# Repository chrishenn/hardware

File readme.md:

# Hardware

Projects based on hardware

- arduino thermistor + pwm fan controller
- keyboard pcb
- arduino led touch slider
- arduino light-sensor-driven light-switch
- prusa mk4s machine and filament settings

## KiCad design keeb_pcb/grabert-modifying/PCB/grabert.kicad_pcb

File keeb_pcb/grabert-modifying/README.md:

# Grabert Keyboard Hardware

💻 🖥️ ⌨️ Open-source ~60% Mechanical Keyboard 🎉

Build Guide and additional information [here](doc/BUILDGUIDE.md)!

<details>
  <summary>Screen and Foot</summary>

</details>
<br/>
<details>
  <summary>PCB Images</summary>

</details>
<br/>

[PCB design video](https://youtu.be/ezk02GJ9iMs)

[Case design video](https://youtu.be/DsW-hKeB3mc)

## Features

- OLED Screen
- Rotary Knob
- Sandwich Mount Case
- POM Switch Plate
- [4 Layout Options](doc/BUILDGUIDE.md#preparation-and-layout-decision)
- 32-bit Microcontroller

### Powered by

- [QMK](https://github.com/qmk/qmk_firmware) ([KoBuss QMK Fork](https://github.com/KoBussLLC/qmk_firmware))
- [VIA](https://caniusevia.com/)

## PCB

This project uses KiCad 6 for electrical CAD

### Electrical Design Constraints

- No diode matrix enabled by LQFP 100 MCU Footprint
- 32-bit STM32 Microcontroller (STM32F072V8T6)
- USB-C
- PCB Mount Switches
- PCB Mount Stabilizers
- Push-Button Encoder
- 0.91" 128x32px I2C OLED Display (SSD1306)

### Changes

- V0 had incorrectly valued bypass capacitors. Testing showed no obvious issues, but it is not preferable.

## CAD

This project uses FreeCAD 0.19 for mechanical CAD

### Required Add-ons

- Assembly 4
- Fasteners
- kicadStepUpMod

### Mechanical Design Contraints

- ~60% Keyboard Layout
- 5 Layout Options
- Push Button Encoder
- OLED 128x32 Screen
- Fully Laser Cut Case
- POM Switch Plate
- 2mm diameter fasteners

### Acrylic Sheet Stackup

Main Case Stackup. "0" is the bottom of the case.

| Sheet Number | FreeCAD "Part" | Thickness | Material   | Shape                                    |
| ------------ | -------------- | --------- | ---------- | ---------------------------------------- |
| 0            | bottom         | 0.125 in  | Acrylic    |                    |
| 1            | closed_spacer  | 0.125 in  | Acrylic    |             |
| 2            | usb_spacer     | 0.125 in  | Acrylic    |  \*with feet   |
| 3            | usb_spacer     | 0.125 in  | Acrylic    |  \*with feet   |
| 4            | switch_plate   | 0.0625 in | POM/Acetal |         |
| 5            | closed_spacer  | 0.125 in  | Acrylic    |             |
| 6            | colored_top    | 0.125 in  | Acrylic    |  |
| 7            | clear_top      | 0.125 in  | Acrylic    |                 |

#### Angled Foot Stackup

Foot stackup. "0" is closest to the case and is on the "top"

| Sheet Number | FreeCAD "Part" | Thickness | Material |
| ------------ | -------------- | --------- | -------- |
| 0            | foot_0         | 0.125 in  | Acrylic  |
| 1            | foot_1         | 0.125 in  | Acrylic  |
| 2            | foot_2         | 0.125 in  | Acrylic  |

## License

MIT License

Copyright (c) 2021 KoBuss LLC

Permission is hereby granted, free of charge, to any person obtaining a copy of this hardware, software, and associated documentation files (the "Product"), to deal in the Product without restriction, including without limitation the rights to use, copy, modify, merge, publish, distribute, sublicense, and/or sell copies of the Product, and to permit persons to whom the Product is furnished to do so, subject to the following conditions:

The above copyright notice and this permission notice shall be included in all copies or substantial portions of the Product.

THE PRODUCT IS PROVIDED "AS IS", WITHOUT WARRANTY OF ANY KIND, EXPRESS OR IMPLIED, INCLUDING BUT NOT LIMITED TO THE WARRANTIES OF MERCHANTABILITY, FITNESS FOR A PARTICULAR PURPOSE AND NONINFRINGEMENT. IN NO EVENT SHALL THE AUTHORS OR COPYRIGHT HOLDERS BE LIABLE FOR ANY CLAIM, DAMAGES OR OTHER LIABILITY, WHETHER IN AN ACTION OF CONTRACT, TORT OR OTHERWISE, ARISING FROM, OUT OF OR IN CONNECTION WITH THE PRODUCT OR THE USE OR OTHER DEALINGS IN THE PRODUCT.

### For the Keyboard Community

You can produce and sell this keyboard. KoBuss LLC is not liable. Creator attribution is preferred but not required.

### License Change?

We initially licensed this under the Creative Commons Attribution-NonCommercial 4.0 International License, but have since decided to change it to MIT.
This would not be appropriate if the product was in production and had been forked/derived, but because we made the license change early on we deemed it acceptable.
If you have any issues with this change, please contact us directly.

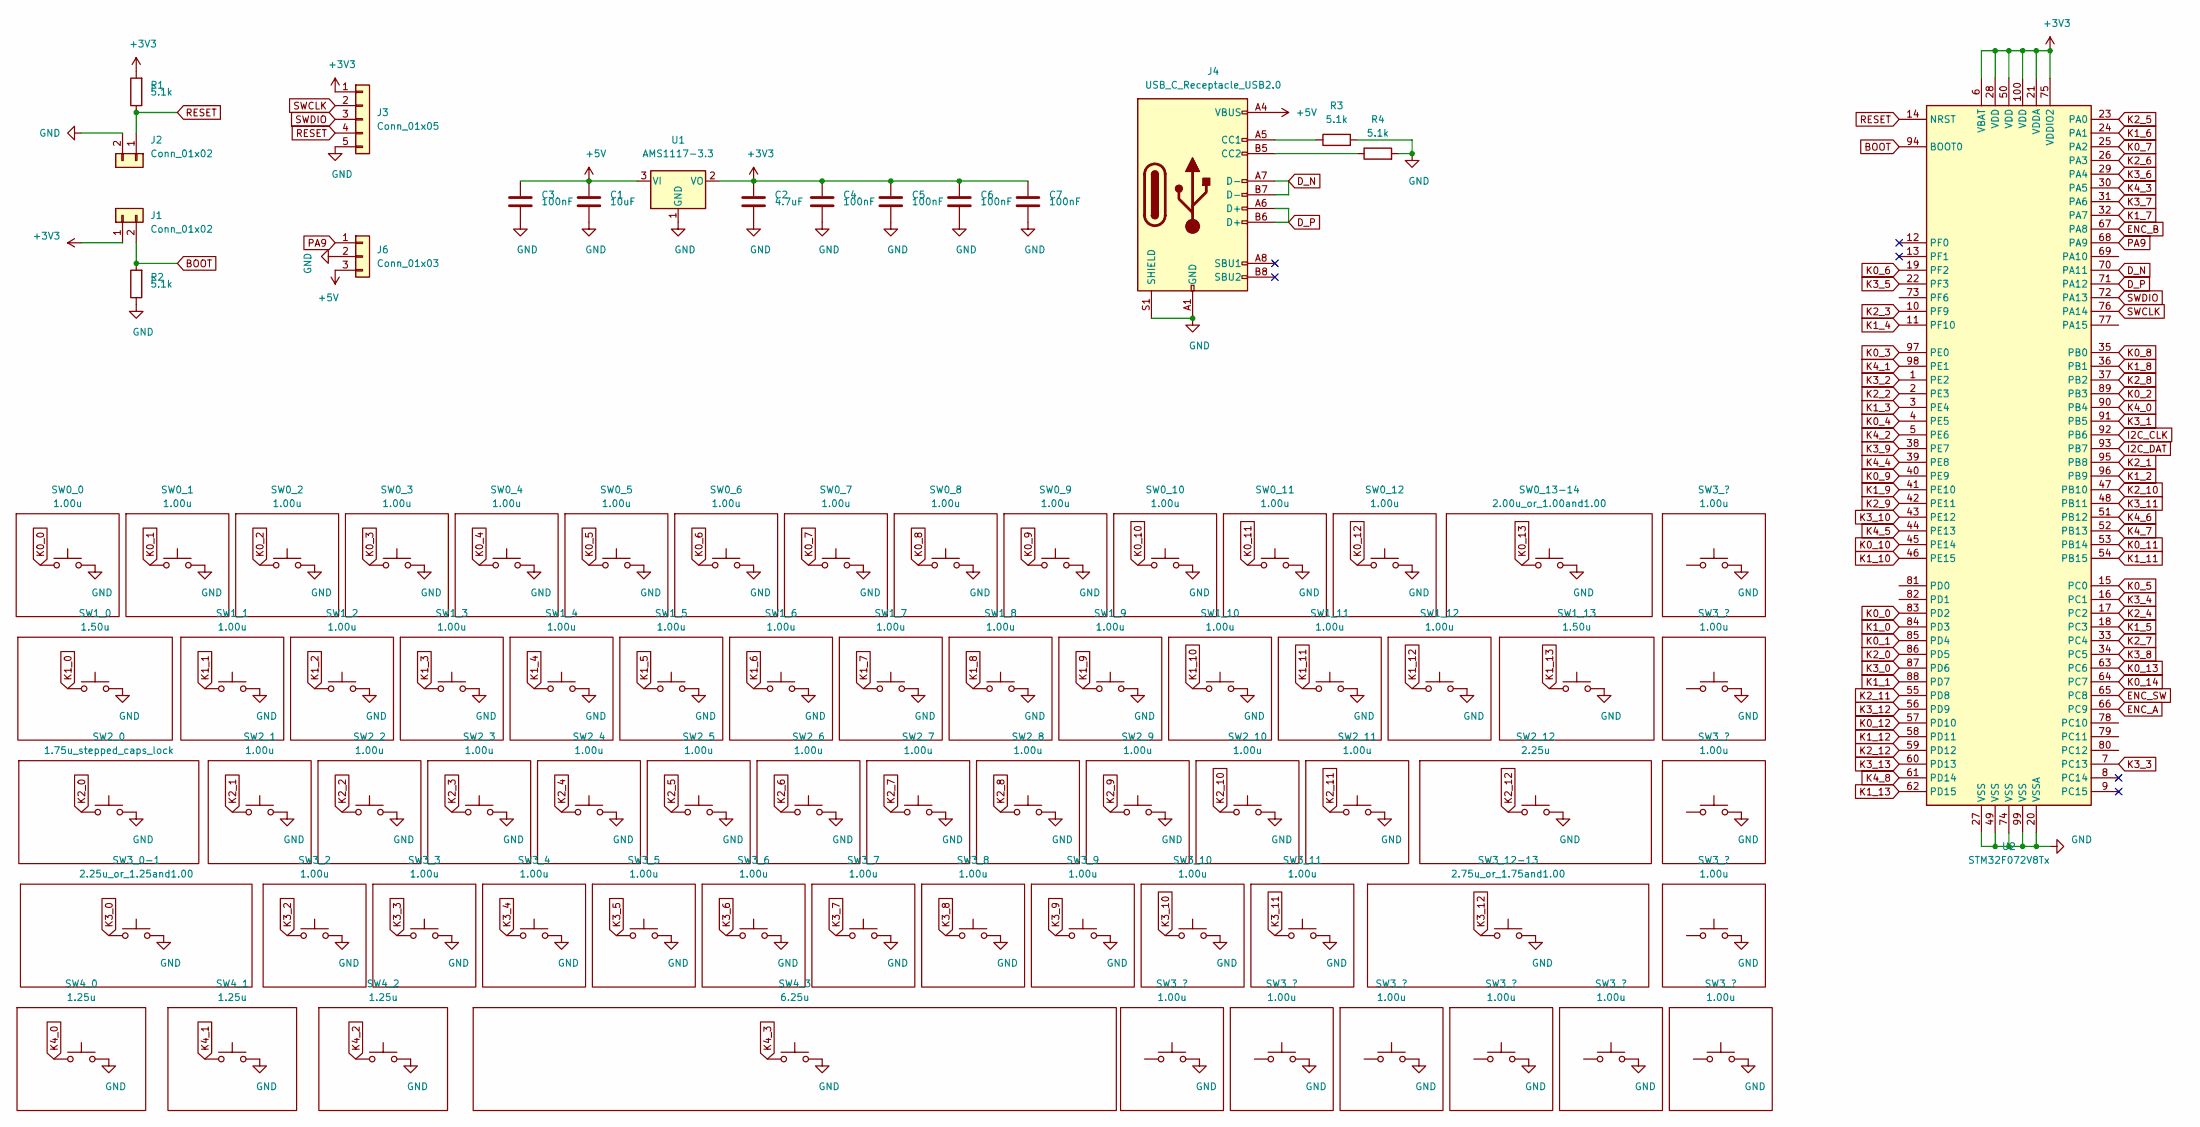
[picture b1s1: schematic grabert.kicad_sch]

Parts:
C1: 10uF; C_0603_1608Metric
C2: 4.7uF; C_0603_1608Metric
C3, C4, C5, C6, C7: 100nF; C_0603_1608Metric
J1, J2: Conn_01x02; PinHeader_1x02_P2.54mm_Vertical
J3: Conn_01x05; PinHeader_1x05_P2.54mm_Vertical
J4: USB_C_Receptacle_USB2.0; U262-161N-4BVC11
J6: Conn_01x03; PinHeader_1x03_P2.54mm_Vertical
R1, R2, R3, R4: 5.1k; R_0603_1608Metric
SW0_0, SW0_1, SW0_2, SW0_3, SW0_4, SW0_5, SW0_6, SW0_7, SW0_8, SW0_9, SW0_10, SW0_11, SW0_12, SW1_1, SW1_2, SW1_3, SW1_4, SW1_5, SW1_6, SW1_7, SW1_8, SW1_9, SW1_10, SW1_11, SW1_12, SW2_1, SW2_2, SW2_3, SW2_4, SW2_5, SW2_6, SW2_7, SW2_8, SW2_9, SW2_10, SW2_11, SW3_2, SW3_3, SW3_4, SW3_5, SW3_6, SW3_7, SW3_8, SW3_9, SW3_10, SW3_11: 1.00u; MX_1u
SW0_13-14: 2.00u_or_1.00and1.00; MX_2.00u_or_1.00and1.00
SW1_0, SW1_13: 1.50u; MX_1.50u
SW2_0: 1.75u_stepped_caps_lock; MX_1.75u_stepped_caps
SW2_12: 2.25u; MX_2.25u
SW3_0-1: 2.25u_or_1.25and1.00; MX_2.25u_or_1.25and1.00
SW3_12-13: 2.75u_or_1.75and1.00; MX_2.75u_or_1.75and1.00
SW4_0, SW4_1, SW4_2: 1.25u; MX_1.25
SW4_3: 6.25u; MX_6.25u
U1: AMS1117-3.3; SOT-223-3_TabPin2
U2: STM32F072V8Tx; LQFP-100_14x14mm_P0.5mm

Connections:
+3V3: C2.1, C4.1, C5.1, C6.1, C7.1, J1.1, J3.1, R1.2, U1.2 (VO), U2.6 (VBAT), U2.21 (VDDA), U2.28 (VDD), U2.50 (VDD), U2.75 (VDDIO2), U2.100 (VDD)
+5V: C1.1, C3.1, J4.A4 (VBUS), J4.A9 (VBUS), J4.B4 (VBUS), J4.B9 (VBUS), J6.3, U1.3 (VI)
BOOT: J1.2, R2.2, U2.94 (BOOT0)
D_N: J4.A7 (D-), J4.B7 (D-), U2.70 (PA11)
D_P: J4.A6 (D+), J4.B6 (D+), U2.71 (PA12)
ENC_A: U2.66 (PC9)
ENC_B: U2.67 (PA8)
ENC_SW: U2.65 (PC8)
GND: C1.2, C2.2, C3.2, C4.2, C5.2, C6.2, C7.2, J2.2, J3.5, J4.A1 (GND), J4.A12 (GND), J4.B1 (GND), J4.B12 (GND), J4.S1 (SHIELD), J6.2, R2.1, R3.2, R4.2, SW0_0.2, SW0_1.2, SW0_2.2, SW0_3.2, SW0_4.2, SW0_5.2, SW0_6.2, SW0_7.2, SW0_8.2, SW0_9.2, SW0_10.2, SW0_11.2, SW0_12.2, SW0_13-14.2, SW0_13-14.4, SW1_0.2, SW1_1.2, SW1_2.2, SW1_3.2, SW1_4.2, SW1_5.2, SW1_6.2, SW1_7.2, SW1_8.2, SW1_9.2, SW1_10.2, SW1_11.2, SW1_12.2, SW1_13.2, SW2_0.2, SW2_1.2, SW2_2.2, SW2_3.2, SW2_4.2, SW2_5.2, SW2_6.2, SW2_7.2, SW2_8.2, SW2_9.2, SW2_10.2, SW2_11.2, SW2_12.2, SW3_0-1.2, SW3_0-1.4, SW3_2.2, SW3_3.2, SW3_4.2, SW3_5.2, SW3_6.2, SW3_7.2, SW3_8.2, SW3_9.2, SW3_10.2, SW3_11.2, SW3_12-13.2, SW3_12-13.4, SW4_0.2, SW4_1.2, SW4_2.2, SW4_3.2, U1.1 (GND), U2.20 (VSSA), U2.27 (VSS), U2.49 (VSS), U2.74 (VSS), U2.99 (VSS); also elsewhere on the board
I2C_CLK: U2.92 (PB6)
I2C_DAT: U2.93 (PB7)
K0_0: SW0_0.1, U2.83 (PD2)
K0_1: SW0_1.1, U2.85 (PD4)
K0_2: SW0_2.1, U2.89 (PB3)
K0_3: SW0_3.1, U2.97 (PE0)
K0_4: SW0_4.1, U2.4 (PE5)
K0_5: SW0_5.1, U2.15 (PC0)
K0_6: SW0_6.1, U2.19 (PF2)
K0_7: SW0_7.1, U2.25 (PA2)
K0_8: SW0_8.1, U2.35 (PB0)
K0_9: SW0_9.1, U2.40 (PE9)
K0_10: SW0_10.1, U2.45 (PE14)
K0_11: SW0_11.1, U2.53 (PB14)
K0_12: SW0_12.1, U2.57 (PD10)
K0_13: SW0_13-14.1, U2.63 (PC6)
K0_14: SW0_13-14.3, U2.64 (PC7)
K1_0: SW1_0.1, U2.84 (PD3)
K1_1: SW1_1.1, U2.88 (PD7)
K1_2: SW1_2.1, U2.96 (PB9)
K1_3: SW1_3.1, U2.3 (PE4)
K1_4: SW1_4.1, U2.11 (PF10)
K1_5: SW1_5.1, U2.18 (PC3)
K1_6: SW1_6.1, U2.24 (PA1)
K1_7: SW1_7.1, U2.32 (PA7)
K1_8: SW1_8.1, U2.36 (PB1)
K1_9: SW1_9.1, U2.41 (PE10)
K1_10: SW1_10.1, U2.46 (PE15)
K1_11: SW1_11.1, U2.54 (PB15)
K1_12: SW1_12.1, U2.58 (PD11)
K1_13: SW1_13.1, U2.62 (PD15)
K2_0: SW2_0.1, U2.86 (PD5)
K2_1: SW2_1.1, U2.95 (PB8)
K2_2: SW2_2.1, U2.2 (PE3)
K2_3: SW2_3.1, U2.10 (PF9)
K2_4: SW2_4.1, U2.17 (PC2)
K2_5: SW2_5.1, U2.23 (PA0)
K2_6: SW2_6.1, U2.26 (PA3)
K2_7: SW2_7.1, U2.33 (PC4)
K2_8: SW2_8.1, U2.37 (PB2)
K2_9: SW2_9.1, U2.42 (PE11)
K2_10: SW2_10.1, U2.47 (PB10)
K2_11: SW2_11.1, U2.55 (PD8)
K2_12: SW2_12.1, U2.59 (PD12)
K3_0: SW3_0-1.1, U2.87 (PD6)
K3_1: SW3_0-1.3, U2.91 (PB5)
K3_2: SW3_2.1, U2.1 (PE2)
K3_3: SW3_3.1, U2.7 (PC13)
K3_4: SW3_4.1, U2.16 (PC1)
K3_5: SW3_5.1, U2.22 (PF3)
K3_6: SW3_6.1, U2.29 (PA4)
K3_7: SW3_7.1, U2.31 (PA6)
K3_8: SW3_8.1, U2.34 (PC5)
K3_9: SW3_9.1, U2.38 (PE7)
K3_10: SW3_10.1, U2.43 (PE12)
K3_11: SW3_11.1, U2.48 (PB11)
K3_12: SW3_12-13.1, U2.56 (PD9)
K3_13: SW3_12-13.3, U2.60 (PD13)
K4_0: SW4_0.1, U2.90 (PB4)
K4_1: SW4_1.1, U2.98 (PE1)
K4_2: SW4_2.1, U2.5 (PE6)
K4_3: SW4_3.1, U2.30 (PA5)
K4_4: U2.39 (PE8); also elsewhere on the board
K4_5: U2.44 (PE13); also elsewhere on the board
K4_6: U2.51 (PB12); also elsewhere on the board
K4_7: U2.52 (PB13); also elsewhere on the board
K4_8: U2.61 (PD14); also elsewhere on the board
unnamed: J4.A5 (CC1), R3.1
unnamed: J4.B5 (CC2), R4.1
PA9: J6.1, U2.68 (PA9)
RESET: J2.1, J3.4, R1.1, U2.14 (NRST)
SWCLK: J3.2, U2.76 (PA14)
SWDIO: J3.3, U2.72 (PA13)

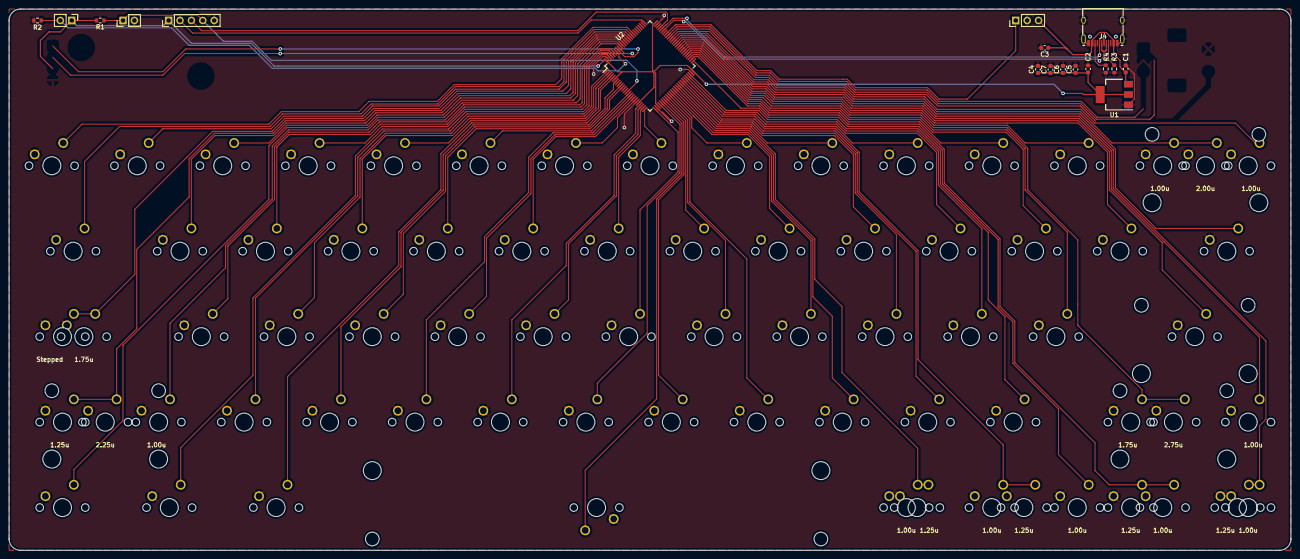
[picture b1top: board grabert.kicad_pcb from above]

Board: 2 copper layers, 285.8 x 120.7 mm, 76 parts (0 on the bottom side), 77 nets.

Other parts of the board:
SW4_4-8: 4x1.25u_or_5x1.00u; MX_4x1.25u_or_5x1.00u

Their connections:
GND: SW4_4-8.2, SW4_4-8.4, SW4_4-8.6, SW4_4-8.8, SW4_4-8.10; also elsewhere on the board
K4_4: SW4_4-8.1; also elsewhere on the board
K4_5: SW4_4-8.3; also elsewhere on the board
K4_6: SW4_4-8.5; also elsewhere on the board
K4_7: SW4_4-8.7; also elsewhere on the board
K4_8: SW4_4-8.9; also elsewhere on the board

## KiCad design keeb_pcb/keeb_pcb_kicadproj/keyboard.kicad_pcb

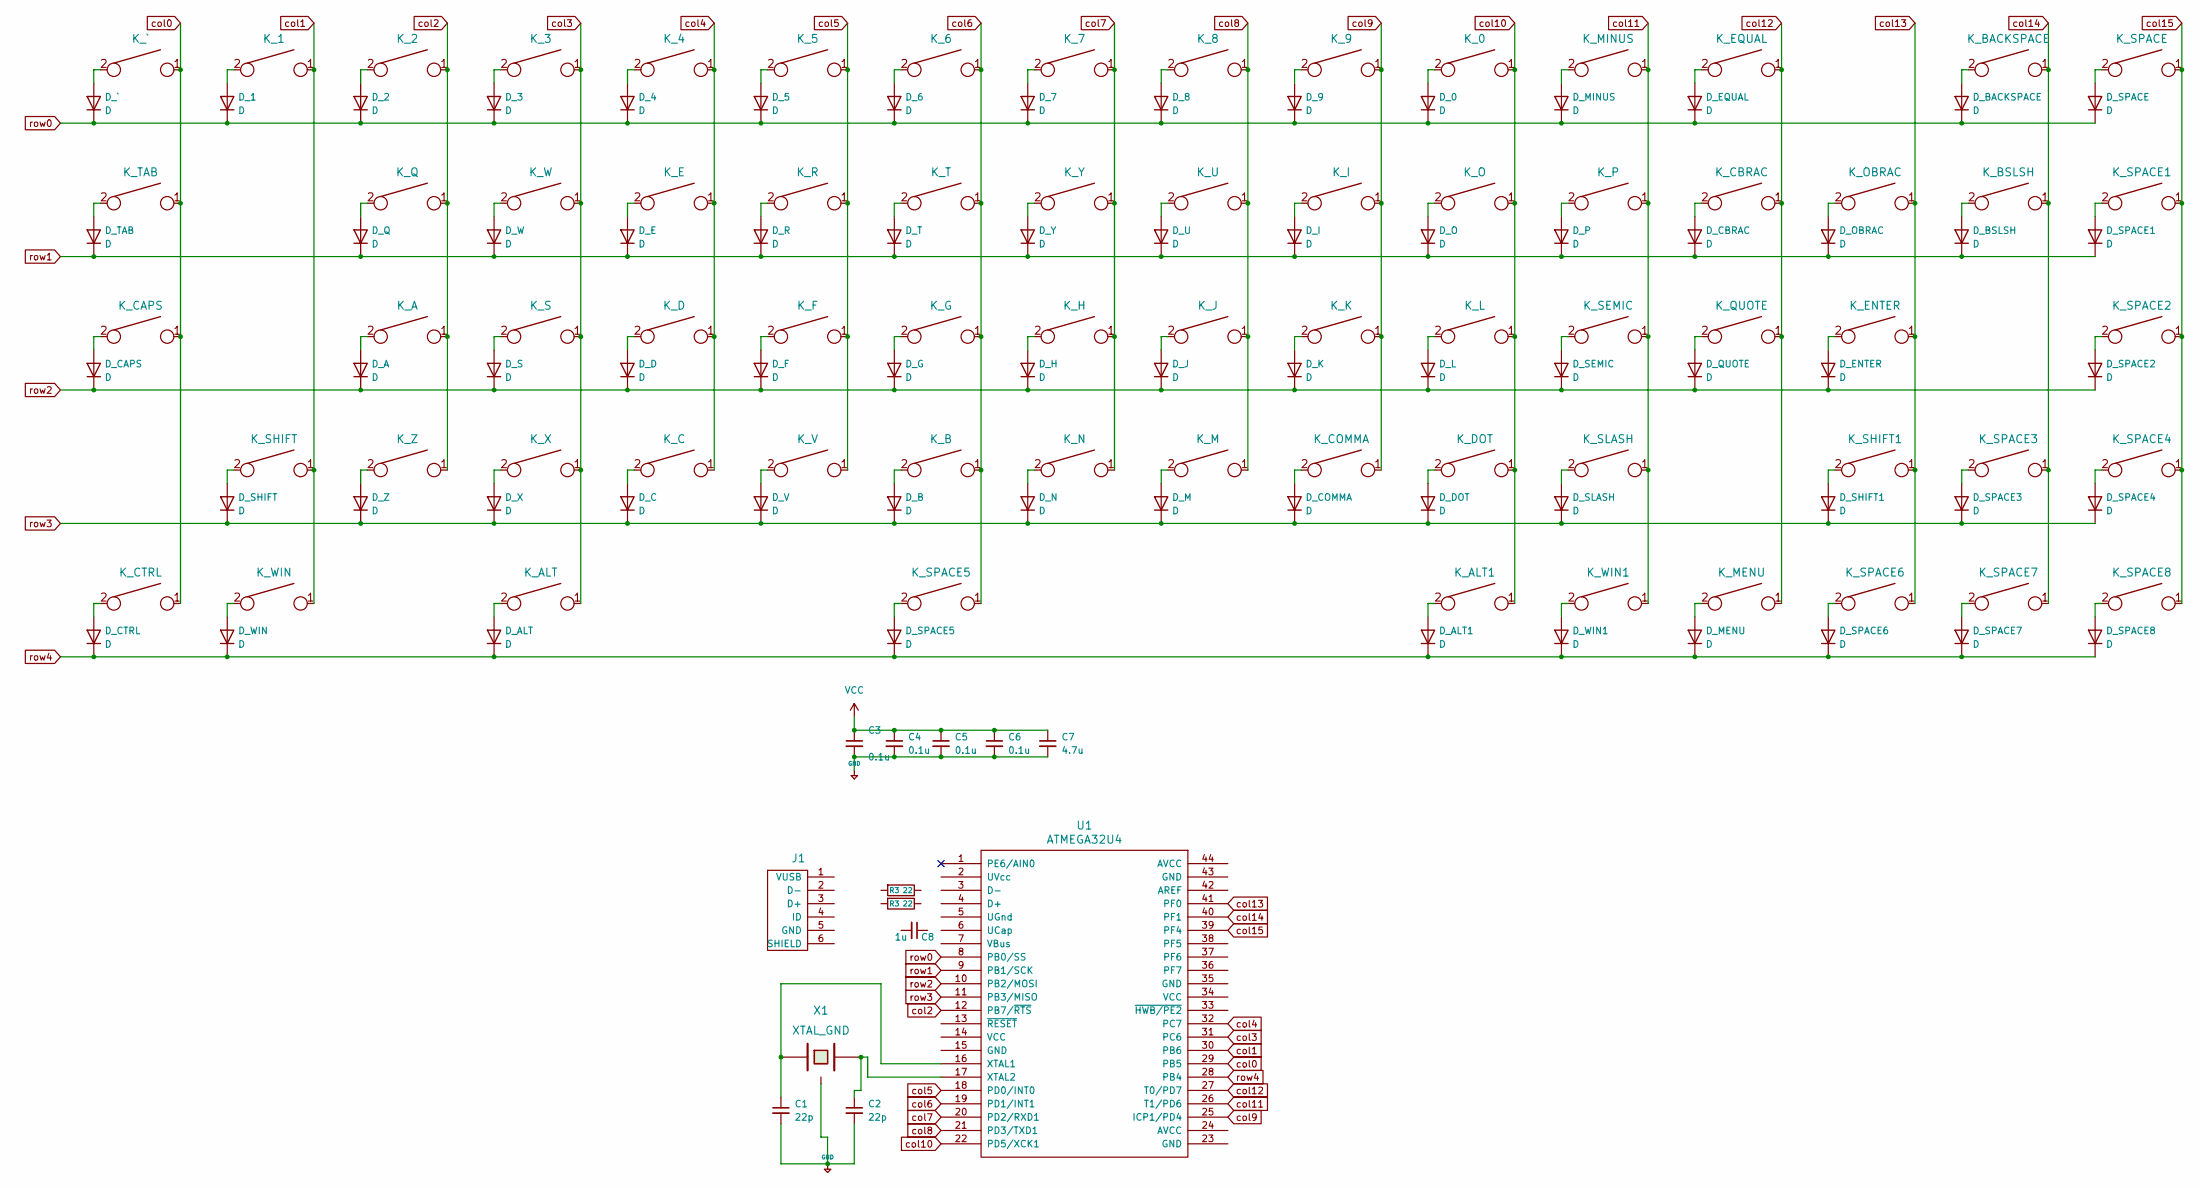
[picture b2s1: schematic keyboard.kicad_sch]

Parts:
C1, C2: 22p
C3, C4, C5, C6: 0.1u
C7: 4.7u
C8: 1u; C_0805_2012Metric_Pad1.15x1.40mm_HandSolder
D_0, D_1, D_2, D_3, D_4, D_5, D_6, D_7, D_8, D_9: D; D_SOD123_axial
D_A: D; D_SOD123_axial
D_ALT, D_ALT1: D; D_SOD123_axial
D_B: D; D_SOD123_axial
D_BACKSPACE: D; D_SOD123_axial
D_BSLSH: D; D_SOD123_axial
D_C: D; D_SOD123_axial
D_CAPS: D; D_SOD123_axial
D_CBRAC: D; D_SOD123_axial
D_COMMA: D; D_SOD123_axial
D_CTRL: D; D_SOD123_axial
D_D: D; D_SOD123_axial
D_DOT: D; D_SOD123_axial
D_E: D; D_SOD123_axial
D_ENTER: D; D_SOD123_axial
D_EQUAL: D; D_SOD123_axial
D_F: D; D_SOD123_axial
D_G: D; D_SOD123_axial
D_H: D; D_SOD123_axial
D_I: D; D_SOD123_axial
D_J: D; D_SOD123_axial
D_K: D; D_SOD123_axial
D_L: D; D_SOD123_axial
D_M: D; D_SOD123_axial
D_MENU: D; D_SOD123_axial
D_MINUS: D; D_SOD123_axial
D_N: D; D_SOD123_axial
D_O: D; D_SOD123_axial
D_OBRAC: D; D_SOD123_axial
D_P: D; D_SOD123_axial
D_Q: D; D_SOD123_axial
D_QUOTE: D; D_SOD123_axial
D_R: D; D_SOD123_axial
D_S: D; D_SOD123_axial
D_SEMIC: D; D_SOD123_axial
D_SHIFT, D_SHIFT1: D; D_SOD123_axial
D_SLASH: D; D_SOD123_axial
D_SPACE, D_SPACE1, D_SPACE2, D_SPACE3, D_SPACE4, D_SPACE5, D_SPACE6, D_SPACE7, D_SPACE8: D; D_SOD123_axial
D_T: D; D_SOD123_axial
D_TAB: D; D_SOD123_axial
D_U: D; D_SOD123_axial
D_V: D; D_SOD123_axial
D_W: D; D_SOD123_axial
D_WIN, D_WIN1: D; D_SOD123_axial
D_X: D; D_SOD123_axial
D_Y: D; D_SOD123_axial
D_Z: D; D_SOD123_axial
D_`: D; D_SOD123_axial
J1: USB_mini_micro_B; USB_miniB_hirose_5S8
K_0, K_1, K_2, K_3, K_4, K_5, K_6, K_7, K_8, K_9: KEYSW; MX-1U-NoLED
K_A: KEYSW; MX-1U-NoLED
K_ALT: KEYSW; MX-1.25U-NoLED
K_ALT1: KEYSW; MX-1U-NoLED
K_B: KEYSW; MX-1U-NoLED
K_BACKSPACE: KEYSW; MX-2U-NoLED
K_BSLSH: KEYSW; MX-1.5U-NoLED
K_C: KEYSW; MX-1U-NoLED
K_CAPS: KEYSW; MX-1.75U-NoLED
K_CBRAC: KEYSW; MX-1U-NoLED
K_COMMA: KEYSW; MX-1U-NoLED
K_CTRL: KEYSW; MX-1.25U-NoLED
K_D: KEYSW; MX-1U-NoLED
K_DOT: KEYSW; MX-1U-NoLED
K_E: KEYSW; MX-1U-NoLED
K_ENTER: KEYSW; MX-2.25U-NoLED
K_EQUAL: KEYSW; MX-1U-NoLED
K_F: KEYSW; MX-1U-NoLED
K_G: KEYSW; MX-1U-NoLED
K_H: KEYSW; MX-1U-NoLED
K_I: KEYSW; MX-1U-NoLED
K_J: KEYSW; MX-1U-NoLED
K_K: KEYSW; MX-1U-NoLED
K_L: KEYSW; MX-1U-NoLED
K_M: KEYSW; MX-1U-NoLED
K_MENU: KEYSW; MX-1U-NoLED
K_MINUS: KEYSW; MX-1U-NoLED
K_N: KEYSW; MX-1U-NoLED
K_O: KEYSW; MX-1U-NoLED
K_OBRAC: KEYSW; MX-1U-NoLED
K_P: KEYSW; MX-1U-NoLED
K_Q: KEYSW; MX-1U-NoLED
K_QUOTE: KEYSW; MX-1U-NoLED
K_R: KEYSW; MX-1U-NoLED
K_S: KEYSW; MX-1U-NoLED
K_SEMIC: KEYSW; MX-1U-NoLED
K_SHIFT: KEYSW; MX-2.25U-NoLED
K_SHIFT1: KEYSW; MX-1.75U-NoLED
K_SLASH: KEYSW; MX-1U-NoLED
K_SPACE, K_SPACE1, K_SPACE2, K_SPACE3, K_SPACE4, K_SPACE6, K_SPACE7, K_SPACE8: KEYSW; MX-1U-NoLED
K_SPACE5: KEYSW; MX-6.25U-NoLED
K_T: KEYSW; MX-1U-NoLED
K_TAB: KEYSW; MX-1.5U-NoLED
K_U: KEYSW; MX-1U-NoLED
K_V: KEYSW; MX-1U-NoLED
K_W: KEYSW; MX-1U-NoLED
K_WIN: KEYSW; MX-1.25U-NoLED
K_WIN1: KEYSW; MX-1U-NoLED
K_X: KEYSW; MX-1U-NoLED
K_Y: KEYSW; MX-1U-NoLED
K_Z: KEYSW; MX-1U-NoLED
K_`: KEYSW; MX-1U-NoLED
R3: 22; R_0805_2012Metric_Pad1.15x1.40mm_HandSolder
U1: ATMEGA32U4; TQFP-44_10x10mm_P0.8mm
X1: XTAL_GND

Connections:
/col0: K_CAPS.1, K_CTRL.1, K_TAB.1, K_`.1, U1.29 (PB5); also elsewhere on the board
/col1: K_1.1, K_SHIFT.1, K_WIN.1, U1.30 (PB6); also elsewhere on the board
/col2: K_2.1, K_A.1, K_Q.1, K_Z.1, U1.12 (PB7/~RTS); also elsewhere on the board
/col3: K_3.1, K_ALT.1, K_S.1, K_W.1, K_X.1, U1.31 (PC6); also elsewhere on the board
/col4: K_4.1, K_C.1, K_D.1, K_E.1, U1.32 (PC7); also elsewhere on the board
/col5: K_5.1, K_F.1, K_R.1, K_V.1, U1.18 (PD0/INT0); also elsewhere on the board
/col6: K_6.1, K_B.1, K_G.1, K_SPACE5.1, K_T.1, U1.19 (PD1/INT1); also elsewhere on the board
/col7: K_7.1, K_H.1, K_N.1, K_Y.1, U1.20 (PD2/RXD1); also elsewhere on the board
/col8: K_8.1, K_J.1, K_M.1, K_U.1, U1.21 (PD3/TXD1); also elsewhere on the board
/col9: K_9.1, K_COMMA.1, K_I.1, K_K.1, U1.25 (ICP1/PD4); also elsewhere on the board
/col10: K_0.1, K_ALT1.1, K_DOT.1, K_L.1, K_O.1, U1.22 (PD5/XCK1); also elsewhere on the board
/col11: K_MINUS.1, K_P.1, K_SEMIC.1, K_SLASH.1, K_WIN1.1, U1.26 (T1/PD6); also elsewhere on the board
/col12: K_CBRAC.1, K_EQUAL.1, K_MENU.1, K_QUOTE.1, U1.27 (T0/PD7); also elsewhere on the board
/col13: K_ENTER.1, K_OBRAC.1, K_SHIFT1.1, K_SPACE6.1, U1.41 (PF0); also elsewhere on the board
/col14: K_BACKSPACE.1, K_BSLSH.1, K_SPACE3.1, K_SPACE7.1, U1.40 (PF1); also elsewhere on the board
/col15: K_SPACE.1, K_SPACE1.1, K_SPACE2.1, K_SPACE4.1, K_SPACE8.1, U1.39 (PF4); also elsewhere on the board
/row0: D_0.1 (K), D_1.1 (K), D_2.1 (K), D_3.1 (K), D_4.1 (K), D_5.1 (K), D_6.1 (K), D_7.1 (K), D_8.1 (K), D_9.1 (K), D_BACKSPACE.1 (K), D_EQUAL.1 (K), D_MINUS.1 (K), D_SPACE.1 (K), D_`.1 (K), U1.8 (PB0/SS); also elsewhere on the board
/row1: D_BSLSH.1 (K), D_CBRAC.1 (K), D_E.1 (K), D_I.1 (K), D_O.1 (K), D_OBRAC.1 (K), D_P.1 (K), D_Q.1 (K), D_R.1 (K), D_SPACE1.1 (K), D_T.1 (K), D_TAB.1 (K), D_U.1 (K), D_W.1 (K), D_Y.1 (K), U1.9 (PB1/SCK); also elsewhere on the board
/row2: D_A.1 (K), D_CAPS.1 (K), D_D.1 (K), D_ENTER.1 (K), D_F.1 (K), D_G.1 (K), D_H.1 (K), D_J.1 (K), D_K.1 (K), D_L.1 (K), D_QUOTE.1 (K), D_S.1 (K), D_SEMIC.1 (K), D_SPACE2.1 (K), U1.10 (PB2/MOSI); also elsewhere on the board
/row3: D_B.1 (K), D_C.1 (K), D_COMMA.1 (K), D_DOT.1 (K), D_M.1 (K), D_N.1 (K), D_SHIFT.1 (K), D_SHIFT1.1 (K), D_SLASH.1 (K), D_SPACE3.1 (K), D_SPACE4.1 (K), D_V.1 (K), D_X.1 (K), D_Z.1 (K), U1.11 (PB3/MISO); also elsewhere on the board
/row4: D_ALT.1 (K), D_ALT1.1 (K), D_CTRL.1 (K), D_MENU.1 (K), D_SPACE5.1 (K), D_SPACE6.1 (K), D_SPACE7.1 (K), D_SPACE8.1 (K), D_WIN.1 (K), D_WIN1.1 (K), U1.28 (PB4); also elsewhere on the board
unnamed: C1.1, U1.16 (XTAL1), X1.1
unnamed: C1.2, C2.2, X1.3
unnamed: C2.1, U1.17 (XTAL2), X1.2
unnamed: C3.1, C4.1, C5.1, C6.1, C7.1
unnamed: C3.2, C4.2, C5.2, C6.2, C7.2
unnamed: D_0.2 (A), K_0.2
unnamed: D_1.2 (A), K_1.2
unnamed: D_2.2 (A), K_2.2
unnamed: D_3.2 (A), K_3.2
unnamed: D_4.2 (A), K_4.2
unnamed: D_5.2 (A), K_5.2
unnamed: D_6.2 (A), K_6.2
unnamed: D_7.2 (A), K_7.2
unnamed: D_8.2 (A), K_8.2
unnamed: D_9.2 (A), K_9.2
unnamed: D_A.2 (A), K_A.2
unnamed: D_ALT1.2 (A), K_ALT1.2
unnamed: D_ALT.2 (A), K_ALT.2
unnamed: D_B.2 (A), K_B.2
unnamed: D_BACKSPACE.2 (A), K_BACKSPACE.2
unnamed: D_BSLSH.2 (A), K_BSLSH.2
unnamed: D_C.2 (A), K_C.2
unnamed: D_CAPS.2 (A), K_CAPS.2
unnamed: D_CBRAC.2 (A), K_CBRAC.2
unnamed: D_COMMA.2 (A), K_COMMA.2
unnamed: D_CTRL.2 (A), K_CTRL.2
unnamed: D_D.2 (A), K_D.2
unnamed: D_DOT.2 (A), K_DOT.2
unnamed: D_E.2 (A), K_E.2
unnamed: D_ENTER.2 (A), K_ENTER.2
unnamed: D_EQUAL.2 (A), K_EQUAL.2
unnamed: D_F.2 (A), K_F.2
unnamed: D_G.2 (A), K_G.2
unnamed: D_H.2 (A), K_H.2
unnamed: D_I.2 (A), K_I.2
unnamed: D_J.2 (A), K_J.2
unnamed: D_K.2 (A), K_K.2
unnamed: D_L.2 (A), K_L.2
unnamed: D_M.2 (A), K_M.2
unnamed: D_MENU.2 (A), K_MENU.2
unnamed: D_MINUS.2 (A), K_MINUS.2
unnamed: D_N.2 (A), K_N.2
unnamed: D_O.2 (A), K_O.2
unnamed: D_OBRAC.2 (A), K_OBRAC.2
unnamed: D_P.2 (A), K_P.2
unnamed: D_Q.2 (A), K_Q.2
unnamed: D_QUOTE.2 (A), K_QUOTE.2
unnamed: D_R.2 (A), K_R.2
unnamed: D_S.2 (A), K_S.2
unnamed: D_SEMIC.2 (A), K_SEMIC.2
unnamed: D_SHIFT1.2 (A), K_SHIFT1.2
unnamed: D_SHIFT.2 (A), K_SHIFT.2
unnamed: D_SLASH.2 (A), K_SLASH.2
unnamed: D_SPACE1.2 (A), K_SPACE1.2
unnamed: D_SPACE2.2 (A), K_SPACE2.2
unnamed: D_SPACE3.2 (A), K_SPACE3.2
unnamed: D_SPACE4.2 (A), K_SPACE4.2
unnamed: D_SPACE5.2 (A), K_SPACE5.2
unnamed: D_SPACE6.2 (A), K_SPACE6.2
unnamed: D_SPACE7.2 (A), K_SPACE7.2
unnamed: D_SPACE8.2 (A), K_SPACE8.2
unnamed: D_SPACE.2 (A), K_SPACE.2
unnamed: D_T.2 (A), K_T.2
unnamed: D_TAB.2 (A), K_TAB.2
unnamed: D_U.2 (A), K_U.2
unnamed: D_V.2 (A), K_V.2
unnamed: D_W.2 (A), K_W.2
unnamed: D_WIN1.2 (A), K_WIN1.2
unnamed: D_WIN.2 (A), K_WIN.2
unnamed: D_X.2 (A), K_X.2
unnamed: D_Y.2 (A), K_Y.2
unnamed: D_Z.2 (A), K_Z.2
unnamed: D_`.2 (A), K_`.2

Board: 2 copper layers, 151 parts (15 on the bottom side), 100 nets, no tracks yet.

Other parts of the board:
C15, C16, C17, C18, C19, C20, C21: 22pF; C_0805_2012Metric_Pad1.15x1.40mm_HandSolder
R9, R10: 10k; R_0805_2012Metric_Pad1.15x1.40mm_HandSolder
R11, R12: 22; R_0805_2012Metric_Pad1.15x1.40mm_HandSolder
SW1: SW_PUSH; SW_SPST_TL3342
U3: ATMEGA32U4; TQFP-44_10x10mm_P0.8mm
USB3: Molex-0548190589; Molex-0548190589-Assembly
X3: XTAL_GND; Crystal_SMD_5032-4Pin_5.0x3.2mm

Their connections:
/col0: U3.29; also elsewhere on the board
/col1: U3.30; also elsewhere on the board
/col2: U3.12; also elsewhere on the board
/col3: U3.31; also elsewhere on the board
/col4: U3.32; also elsewhere on the board
/col5: U3.18; also elsewhere on the board
/col6: U3.19; also elsewhere on the board
/col7: U3.20; also elsewhere on the board
/col8: U3.21; also elsewhere on the board
/col9: U3.25; also elsewhere on the board
/col10: U3.22; also elsewhere on the board
/col11: U3.26; also elsewhere on the board
/col12: U3.27; also elsewhere on the board
/col13: U3.41; also elsewhere on the board
/col14: U3.40; also elsewhere on the board
/col15: U3.39; also elsewhere on the board
/row0: U3.8; also elsewhere on the board
/row1: U3.9; also elsewhere on the board
/row2: U3.10; also elsewhere on the board
/row3: U3.11; also elsewhere on the board
/row4: U3.28; also elsewhere on the board
GND: C15.2, C16.2, C17.2, C18.2, C19.2, C20.2, C21.2, R10.2, SW1.1, U3.5, U3.15, U3.23, USB3.1, X3.2, X3.4
unnamed: C15.1, U3.16, X3.1
unnamed: C16.1, U3.17, X3.3
unnamed: C17.1, U3.6
unnamed: R9.1, SW1.2, U3.13
unnamed: R10.1, U3.33
unnamed: R11.1, U3.3
unnamed: R12.1, U3.4
unnamed: R11.2, USB3.2
unnamed: R12.2, USB3.3
VCC: C18.1, C19.1, C20.1, C21.1, R9.2, U3.2, U3.14, U3.24, USB3.5

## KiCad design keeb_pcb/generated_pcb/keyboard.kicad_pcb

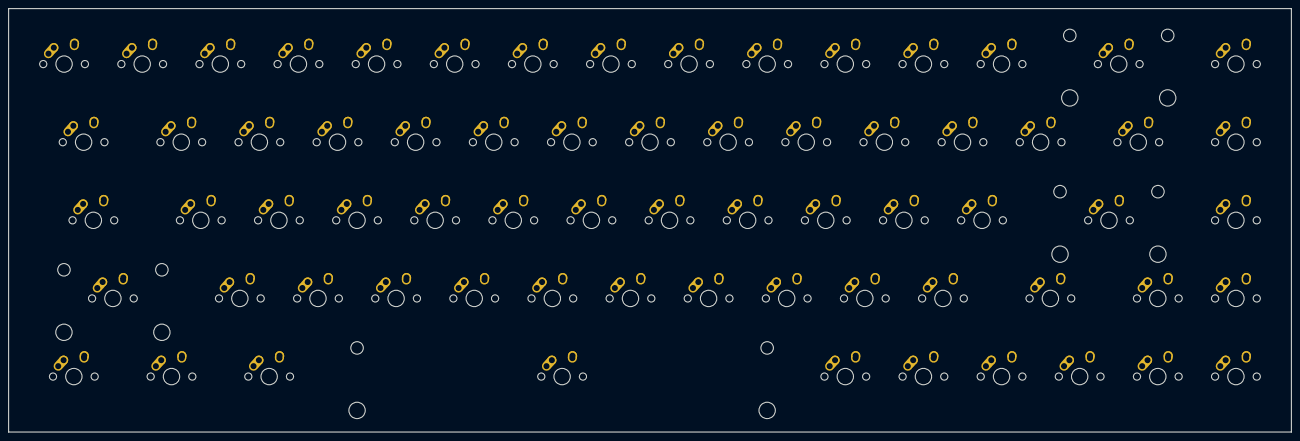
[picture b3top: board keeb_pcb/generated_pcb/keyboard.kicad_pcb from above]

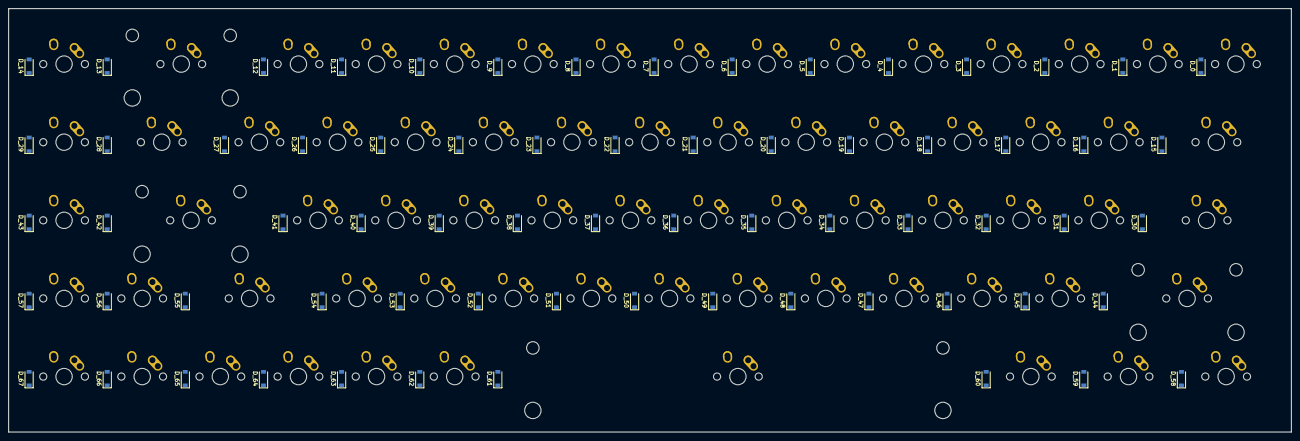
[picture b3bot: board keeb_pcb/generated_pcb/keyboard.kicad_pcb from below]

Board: 2 copper layers, 312.8 x 103.2 mm, 136 parts (68 on the bottom side), 89 nets, no tracks yet.

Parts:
D_0, D_1, D_2, D_3, D_4, D_5, D_6, D_7, D_8, D_9, D_10, D_11, D_12, D_13, D_14, D_15, D_16, D_17, D_18, D_19, D_20, D_21, D_22, D_23, D_24, D_25, D_26, D_27, D_28, D_29, D_30, D_31, D_32, D_33, D_34, D_35, D_36, D_37, D_38, D_39, D_40, D_41, D_42, D_43, D_44, D_45, D_46, D_47, D_48, D_49, D_50, D_51, D_52, D_53, D_54, D_55, D_56, D_57, D_58, D_59, D_60, D_61, D_62, D_63, D_64, D_65, D_66, D_67: D; D_SOD-123
K_0, K_1, K_2, K_3, K_4, K_5, K_6, K_7, K_8, K_9, K_10, K_11, K_12, K_14, K_16, K_17, K_18, K_19, K_20, K_21, K_22, K_23, K_24, K_25, K_26, K_27, K_29, K_31, K_32, K_33, K_34, K_35, K_36, K_37, K_38, K_39, K_40, K_41, K_43, K_45, K_46, K_47, K_48, K_49, K_50, K_51, K_52, K_53, K_54, K_56, K_57, K_62, K_63, K_64, K_65, K_66, K_67: KEYSW; MX-1U-NoLED
K_13: KEYSW; MX-2U-NoLED
K_15, K_28: KEYSW; MX-1.5U-NoLED
K_30, K_55: KEYSW; MX-1.75U-NoLED
K_42, K_44: KEYSW; MX-2.25U-NoLED
K_58, K_59, K_60: KEYSW; MX-1.25U-NoLED
K_61: KEYSW; MX-6.25U-NoLED

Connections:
unnamed: D_0.2, K_0.2
unnamed: D_1.2, K_1.2
unnamed: D_2.2, K_2.2
unnamed: D_3.2, K_3.2
unnamed: D_4.2, K_4.2
unnamed: D_5.2, K_5.2
unnamed: D_6.2, K_6.2
unnamed: D_7.2, K_7.2
unnamed: D_8.2, K_8.2
unnamed: D_9.2, K_9.2
unnamed: D_10.2, K_10.2
unnamed: D_11.2, K_11.2
unnamed: D_12.2, K_12.2
unnamed: D_13.2, K_13.2
unnamed: D_14.2, K_14.2
unnamed: D_15.2, K_15.2
unnamed: D_16.2, K_16.2
unnamed: D_17.2, K_17.2
unnamed: D_18.2, K_18.2
unnamed: D_19.2, K_19.2
unnamed: D_20.2, K_20.2
unnamed: D_21.2, K_21.2
unnamed: D_22.2, K_22.2
unnamed: D_23.2, K_23.2
unnamed: D_24.2, K_24.2
unnamed: D_25.2, K_25.2
unnamed: D_26.2, K_26.2
unnamed: D_27.2, K_27.2
unnamed: D_28.2, K_28.2
unnamed: D_29.2, K_29.2
unnamed: D_30.2, K_30.2
unnamed: D_31.2, K_31.2
unnamed: D_32.2, K_32.2
unnamed: D_33.2, K_33.2
unnamed: D_34.2, K_34.2
unnamed: D_35.2, K_35.2
unnamed: D_36.2, K_36.2
unnamed: D_37.2, K_37.2
unnamed: D_38.2, K_38.2
unnamed: D_39.2, K_39.2
unnamed: D_40.2, K_40.2
unnamed: D_41.2, K_41.2
unnamed: D_42.2, K_42.2
unnamed: D_43.2, K_43.2
unnamed: D_44.2, K_44.2
unnamed: D_45.2, K_45.2
unnamed: D_46.2, K_46.2
unnamed: D_47.2, K_47.2
unnamed: D_48.2, K_48.2
unnamed: D_49.2, K_49.2
unnamed: D_50.2, K_50.2
unnamed: D_51.2, K_51.2
unnamed: D_52.2, K_52.2
unnamed: D_53.2, K_53.2
unnamed: D_54.2, K_54.2
unnamed: D_55.2, K_55.2
unnamed: D_56.2, K_56.2
unnamed: D_57.2, K_57.2
unnamed: D_58.2, K_58.2
unnamed: D_59.2, K_59.2
unnamed: D_60.2, K_60.2
unnamed: D_61.2, K_61.2
unnamed: D_62.2, K_62.2
unnamed: D_63.2, K_63.2
unnamed: D_64.2, K_64.2
unnamed: D_65.2, K_65.2
unnamed: D_66.2, K_66.2
unnamed: D_67.2, K_67.2
col0: K_0.1, K_15.1, K_30.1, K_58.1
col1: K_1.1, K_44.1, K_59.1
col2: K_2.1, K_16.1, K_31.1, K_45.1
col3: K_3.1, K_17.1, K_32.1, K_46.1, K_60.1
col4: K_4.1, K_18.1, K_33.1, K_47.1
col5: K_5.1, K_19.1, K_34.1, K_48.1
col6: K_6.1, K_20.1, K_35.1, K_49.1, K_61.1
col7: K_7.1, K_21.1, K_36.1, K_50.1
col8: K_8.1, K_22.1, K_37.1, K_51.1
col9: K_9.1, K_23.1, K_38.1, K_52.1
col10: K_10.1, K_24.1, K_39.1, K_53.1, K_62.1
col11: K_11.1, K_25.1, K_40.1, K_54.1, K_63.1
col12: K_12.1, K_26.1, K_41.1, K_64.1
col13: K_27.1, K_42.1, K_55.1, K_65.1
col14: K_13.1, K_28.1, K_56.1, K_66.1
col15: K_14.1, K_29.1, K_43.1, K_57.1, K_67.1
row0: D_0.1, D_1.1, D_2.1, D_3.1, D_4.1, D_5.1, D_6.1, D_7.1, D_8.1, D_9.1, D_10.1, D_11.1, D_12.1, D_13.1, D_14.1
row1: D_15.1, D_16.1, D_17.1, D_18.1, D_19.1, D_20.1, D_21.1, D_22.1, D_23.1, D_24.1, D_25.1, D_26.1, D_27.1, D_28.1, D_29.1
row2: D_30.1, D_31.1, D_32.1, D_33.1, D_34.1, D_35.1, D_36.1, D_37.1, D_38.1, D_39.1, D_40.1, D_41.1, D_42.1, D_43.1
row3: D_44.1, D_45.1, D_46.1, D_47.1, D_48.1, D_49.1, D_50.1, D_51.1, D_52.1, D_53.1, D_54.1, D_55.1, D_56.1, D_57.1
row4: D_58.1, D_59.1, D_60.1, D_61.1, D_62.1, D_63.1, D_64.1, D_65.1, D_66.1, D_67.1

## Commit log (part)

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2025-09-23 init
2025-11-26 cleanup
2025-12-04 rm node_modules
2025-12-04 add laundry card
2026-05-10 feat: static ip
2026-05-10 feat: esp32 light switch
2026-05-10 chore: mk4s config bundle update
